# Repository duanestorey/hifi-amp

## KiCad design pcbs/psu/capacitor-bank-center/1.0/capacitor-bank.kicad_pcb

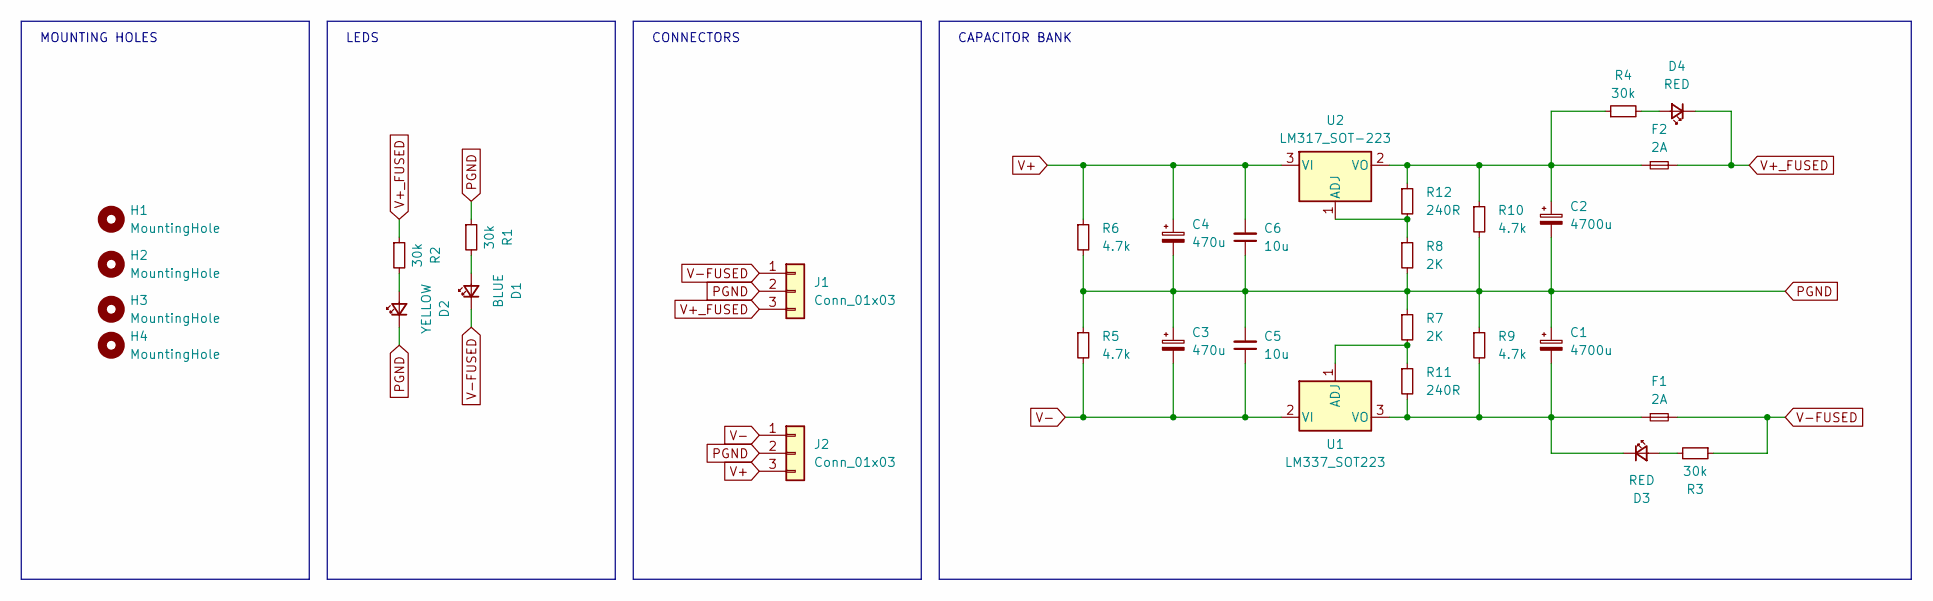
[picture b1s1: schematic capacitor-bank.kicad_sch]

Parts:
C1, C2: 4700u; CP_Radial_D16.0mm_P7.50mm
C3, C4: 470u; CP_Radial_D8.0mm_P5.00mm
C5, C6: 10u; C_1206_3216Metric_Pad1.33x1.80mm_HandSolder
D1: BLUE; LED_0805_2012Metric_Pad1.15x1.40mm_HandSolder
D2: YELLOW; LED_0805_2012Metric_Pad1.15x1.40mm_HandSolder
D3, D4: RED; LED_0805_2012Metric_Pad1.15x1.40mm_HandSolder
F1, F2: 2A; Aliexpress Fuse 5x20
H1, H2, H3, H4: MountingHole; MountingHole_3.2mm_M3_DIN965_Pad_TopBottom
J1, J2: Conn_01x03; JST_VH_B3P-VH-B_1x03_P3.96mm_Vertical
R1, R2, R3, R4: 30k; R_0805_2012Metric_Pad1.20x1.40mm_HandSolder
R5, R6, R9, R10: 4.7k; R_0805_2012Metric_Pad1.20x1.40mm_HandSolder
R7, R8: 2K; R_0805_2012Metric_Pad1.20x1.40mm_HandSolder
R11, R12: 240R; R_0805_2012Metric_Pad1.20x1.40mm_HandSolder
U1: LM337_SOT223; SOT-223-3_TabPin2
U2: LM317_SOT-223; SOT-223-3_TabPin2

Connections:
unnamed: D1.2 (A), R1.2
unnamed: D2.2 (A), R2.2
unnamed: D3.2 (A), R3.2
unnamed: C1.2, D3.1 (K), F1.1, R9.2, R11.2, U1.3 (VO)
unnamed: D4.2 (A), R4.2
unnamed: R7.2, R11.1, U1.1 (ADJ)
unnamed: R8.1, R12.2, U2.1 (ADJ)
unnamed: C2.1, F2.1, R4.1, R10.1, R12.1, U2.2 (VO)
PGND: C1.1, C2.2, C3.1, C4.2, C5.2, C6.1, D2.1 (K), J1.2, J2.2, R1.1, R5.1, R6.2, R7.1, R8.2, R9.1, R10.2
V+: C4.1, C6.2, J2.3, R6.1, U2.3 (VI)
V+_FUSED: D4.1 (K), F2.2, J1.3, R2.1
V-: C3.2, C5.1, J2.1, R5.2, U1.2 (VI)
V-FUSED: D1.1 (K), F1.2, J1.1, R3.1

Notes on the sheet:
CAPACITOR BANK
MOUNTING HOLES
LEDS
CONNECTORS

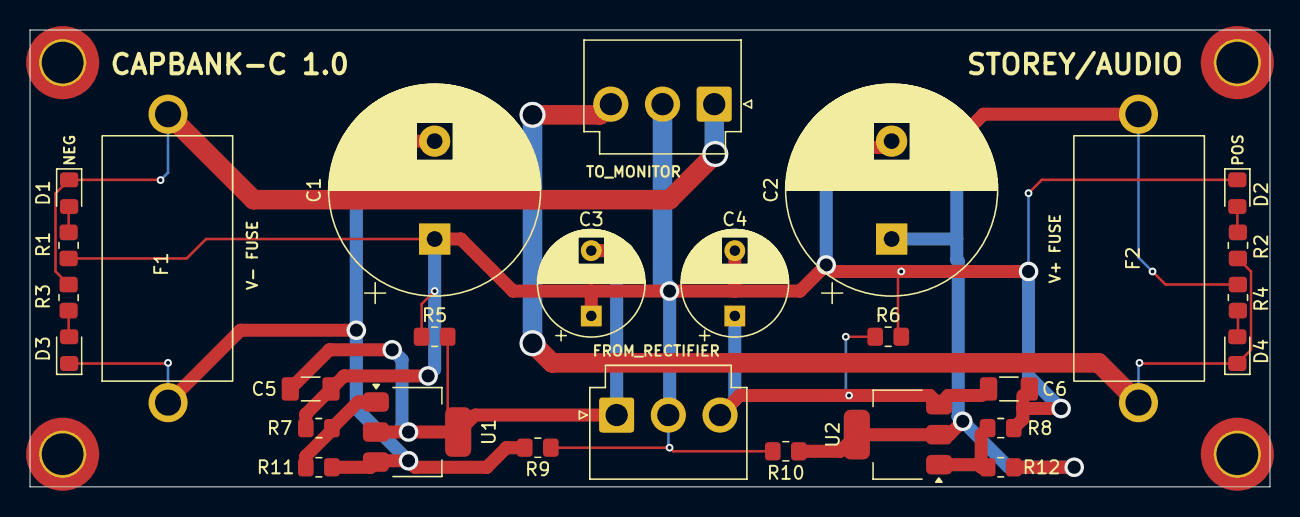
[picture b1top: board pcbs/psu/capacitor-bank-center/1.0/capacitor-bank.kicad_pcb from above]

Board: 2 copper layers, 95.0 x 35.0 mm, 32 parts (0 on the bottom side), 13 nets.

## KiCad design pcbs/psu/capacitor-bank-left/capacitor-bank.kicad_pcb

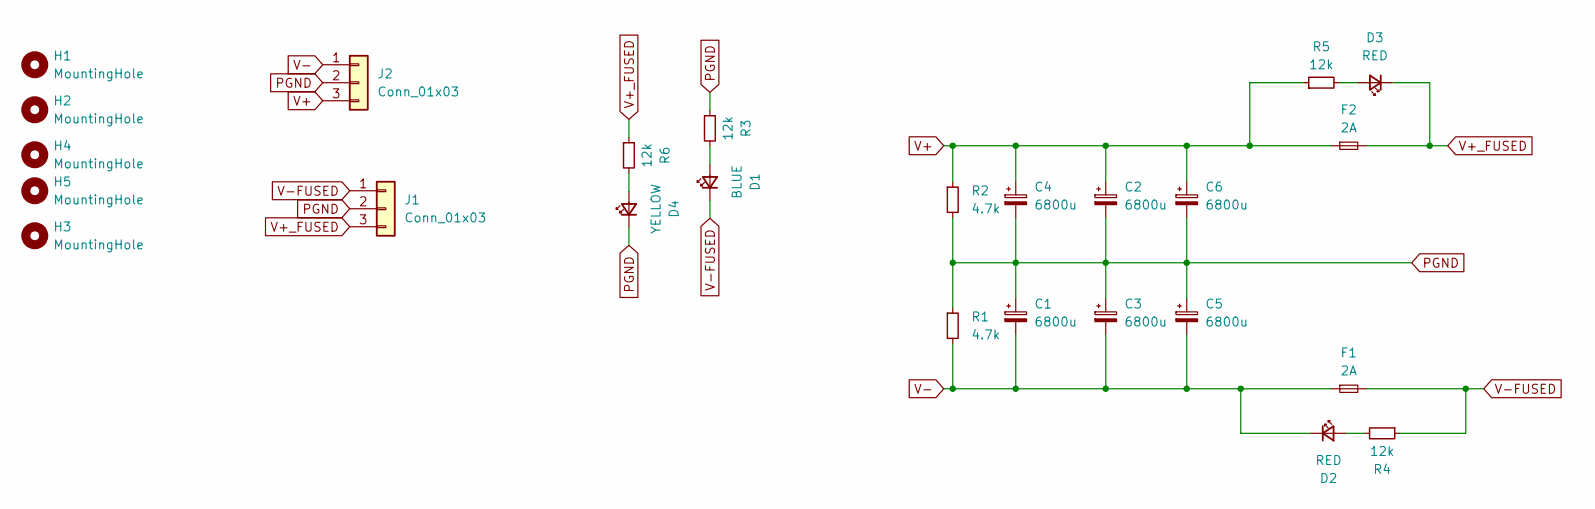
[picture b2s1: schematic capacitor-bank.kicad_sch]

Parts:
C1, C2, C3, C4, C5, C6: 6800u; CP_Radial_D25.0mm_P10.00mm_SnapIn
D1: BLUE; LED_0805_2012Metric_Pad1.15x1.40mm_HandSolder
D2, D3: RED; LED_0805_2012Metric_Pad1.15x1.40mm_HandSolder
D4: YELLOW; LED_0805_2012Metric_Pad1.15x1.40mm_HandSolder
F1, F2: 2A; Aliexpress Fuse 5x20
H1, H2, H3, H4, H5: MountingHole; MountingHole_3.2mm_M3_DIN965_Pad_TopBottom
J1, J2: Conn_01x03; JST_VH_B3P-VH-B_1x03_P3.96mm_Vertical
R1, R2: 4.7k; R_0805_2012Metric_Pad1.20x1.40mm_HandSolder
R3, R4, R5, R6: 12k; R_0805_2012Metric_Pad1.20x1.40mm_HandSolder

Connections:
unnamed: D1.2 (A), R3.2
unnamed: D2.2 (A), R4.2
unnamed: D3.2 (A), R5.2
unnamed: D4.2 (A), R6.2
PGND: C1.1, C2.2, C3.1, C4.2, C5.1, C6.2, D4.1 (K), J1.2, J2.2, R1.1, R2.2, R3.1
V+: C2.1, C4.1, C6.1, F2.1, J2.3, R2.1, R5.1
V+_FUSED: D3.1 (K), F2.2, J1.3, R6.1
V-: C1.2, C3.2, C5.2, D2.1 (K), F1.1, J2.1, R1.2
V-FUSED: D1.1 (K), F1.2, J1.1, R4.1

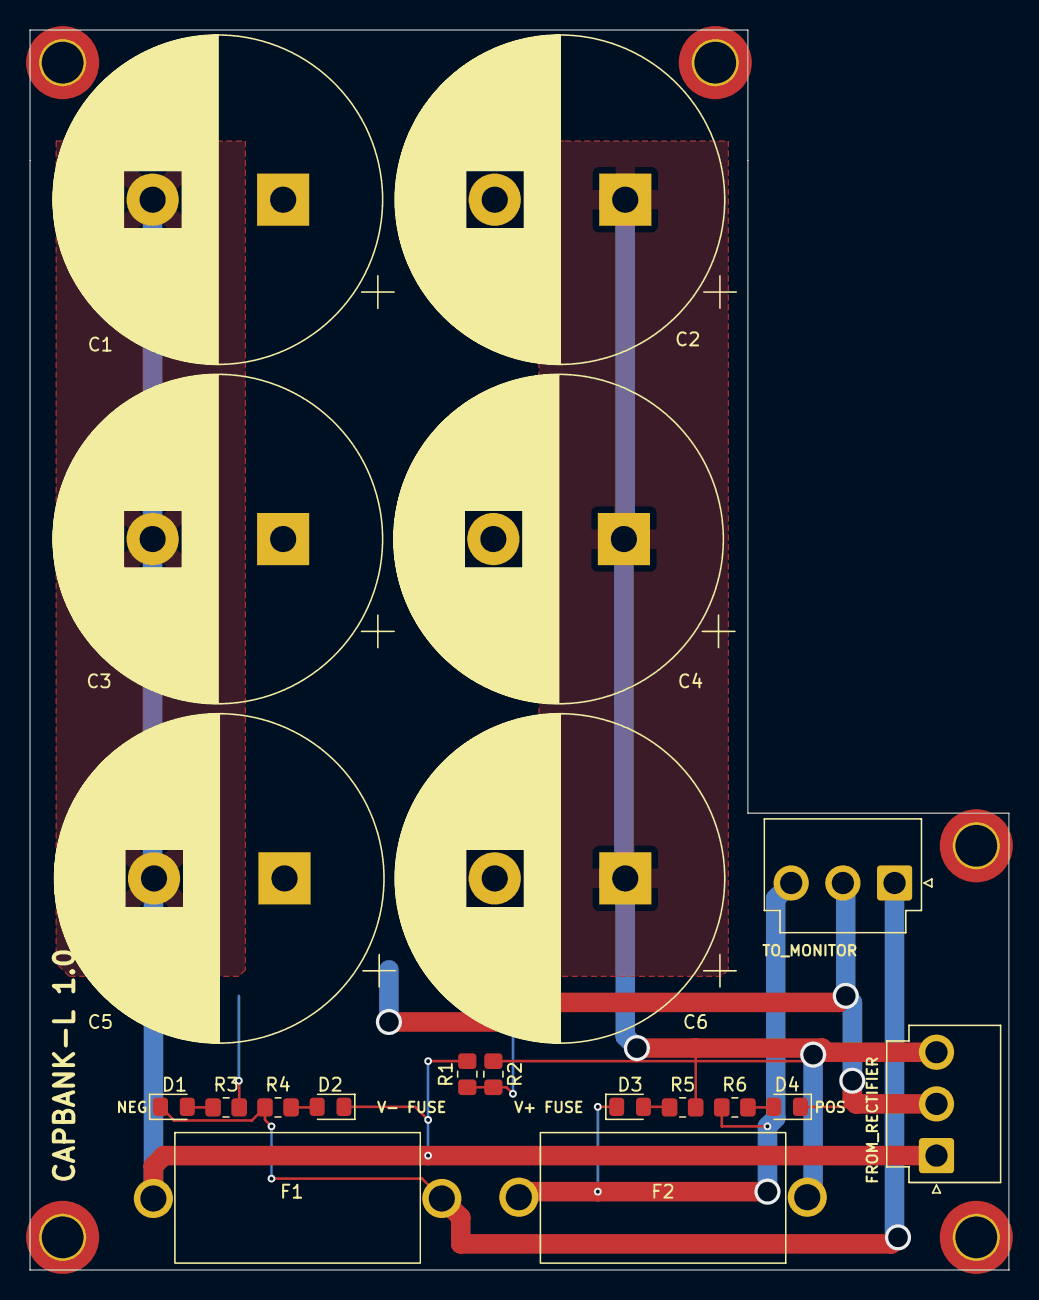
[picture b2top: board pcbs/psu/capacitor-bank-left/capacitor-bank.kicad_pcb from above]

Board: 2 copper layers, 75.0 x 95.0 mm, 25 parts (0 on the bottom side), 9 nets.

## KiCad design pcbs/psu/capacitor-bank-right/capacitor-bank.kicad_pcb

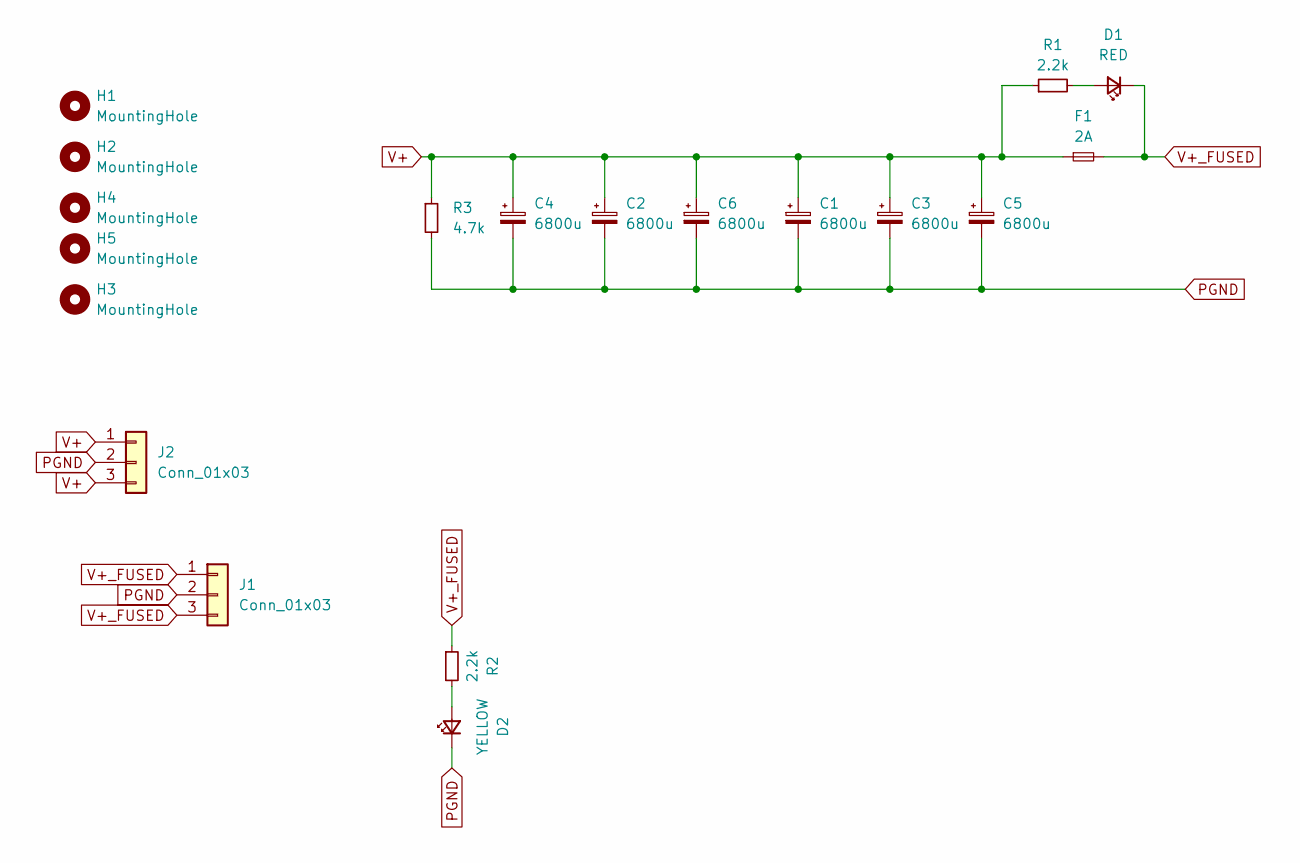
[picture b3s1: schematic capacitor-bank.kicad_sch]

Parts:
C1, C2, C3, C4, C5, C6: 6800u; CP_Radial_D25.0mm_P10.00mm_SnapIn
D1: RED; LED_0805_2012Metric_Pad1.15x1.40mm_HandSolder
D2: YELLOW; LED_0805_2012Metric_Pad1.15x1.40mm_HandSolder
F1: 2A; Aliexpress Fuse 5x20
H1, H2, H3, H4, H5: MountingHole; MountingHole_3.2mm_M3_DIN965_Pad_TopBottom
J1, J2: Conn_01x03; JST_VH_B3P-VH-B_1x03_P3.96mm_Vertical
R1, R2: 2.2k; R_0805_2012Metric_Pad1.20x1.40mm_HandSolder
R3: 4.7k; R_0805_2012Metric_Pad1.20x1.40mm_HandSolder

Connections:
unnamed: D1.2 (A), R1.2
unnamed: D2.2 (A), R2.2
PGND: C1.2, C2.2, C3.2, C4.2, C5.2, C6.2, D2.1 (K), J1.2, J2.2, R3.2
V+: C1.1, C2.1, C3.1, C4.1, C5.1, C6.1, F1.1, J2.1, J2.3, R1.1, R3.1
V+_FUSED: D1.1 (K), F1.2, J1.1, J1.3, R2.1

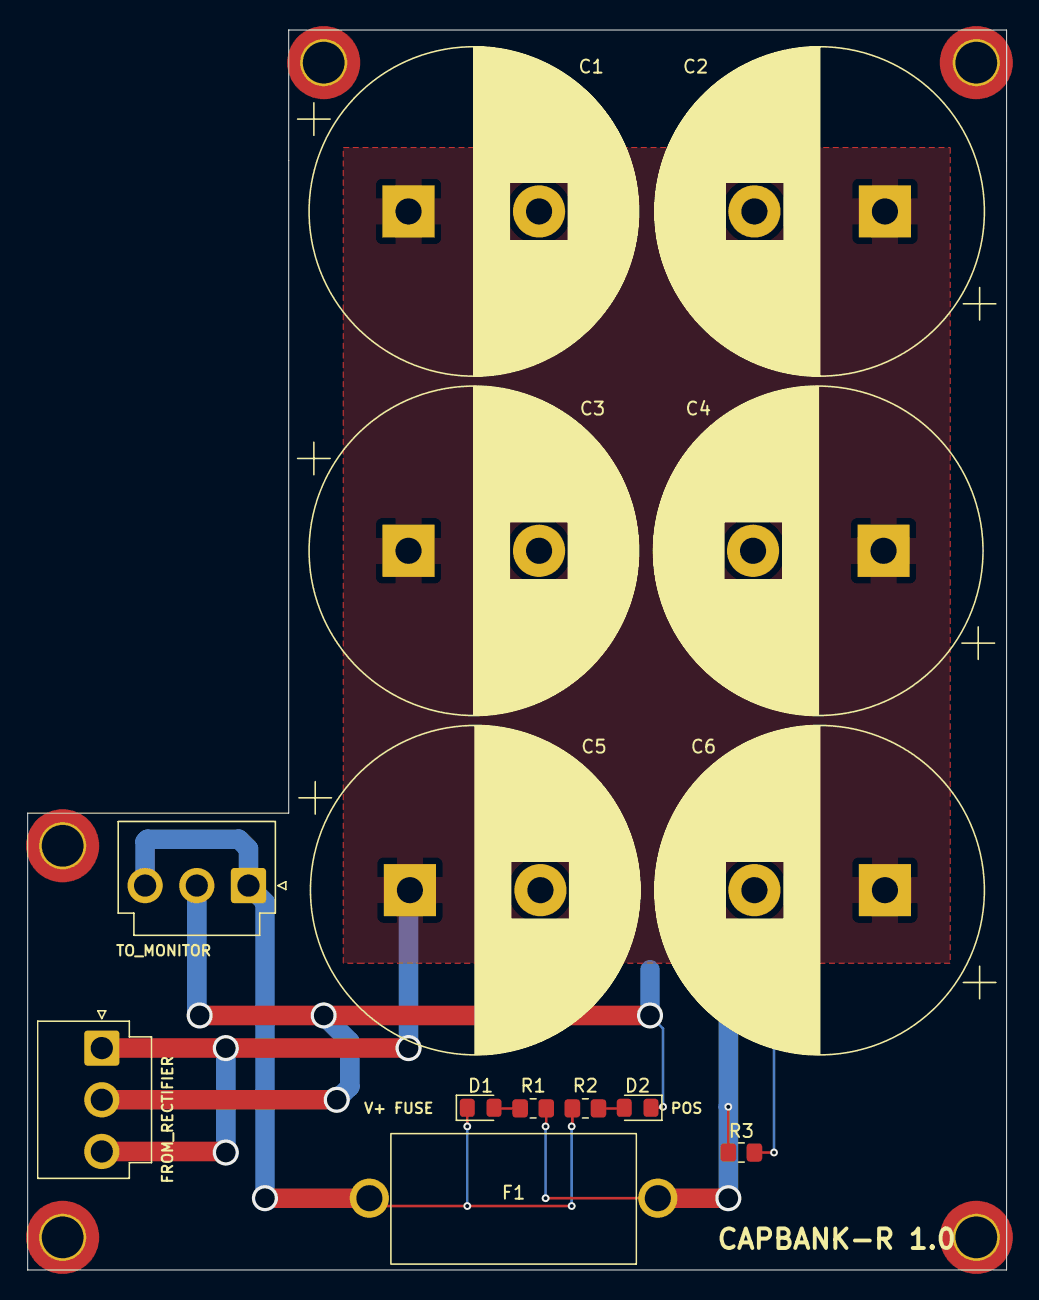
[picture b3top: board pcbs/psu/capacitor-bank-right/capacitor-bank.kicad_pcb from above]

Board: 2 copper layers, 75.0 x 95.0 mm, 19 parts (0 on the bottom side), 5 nets.

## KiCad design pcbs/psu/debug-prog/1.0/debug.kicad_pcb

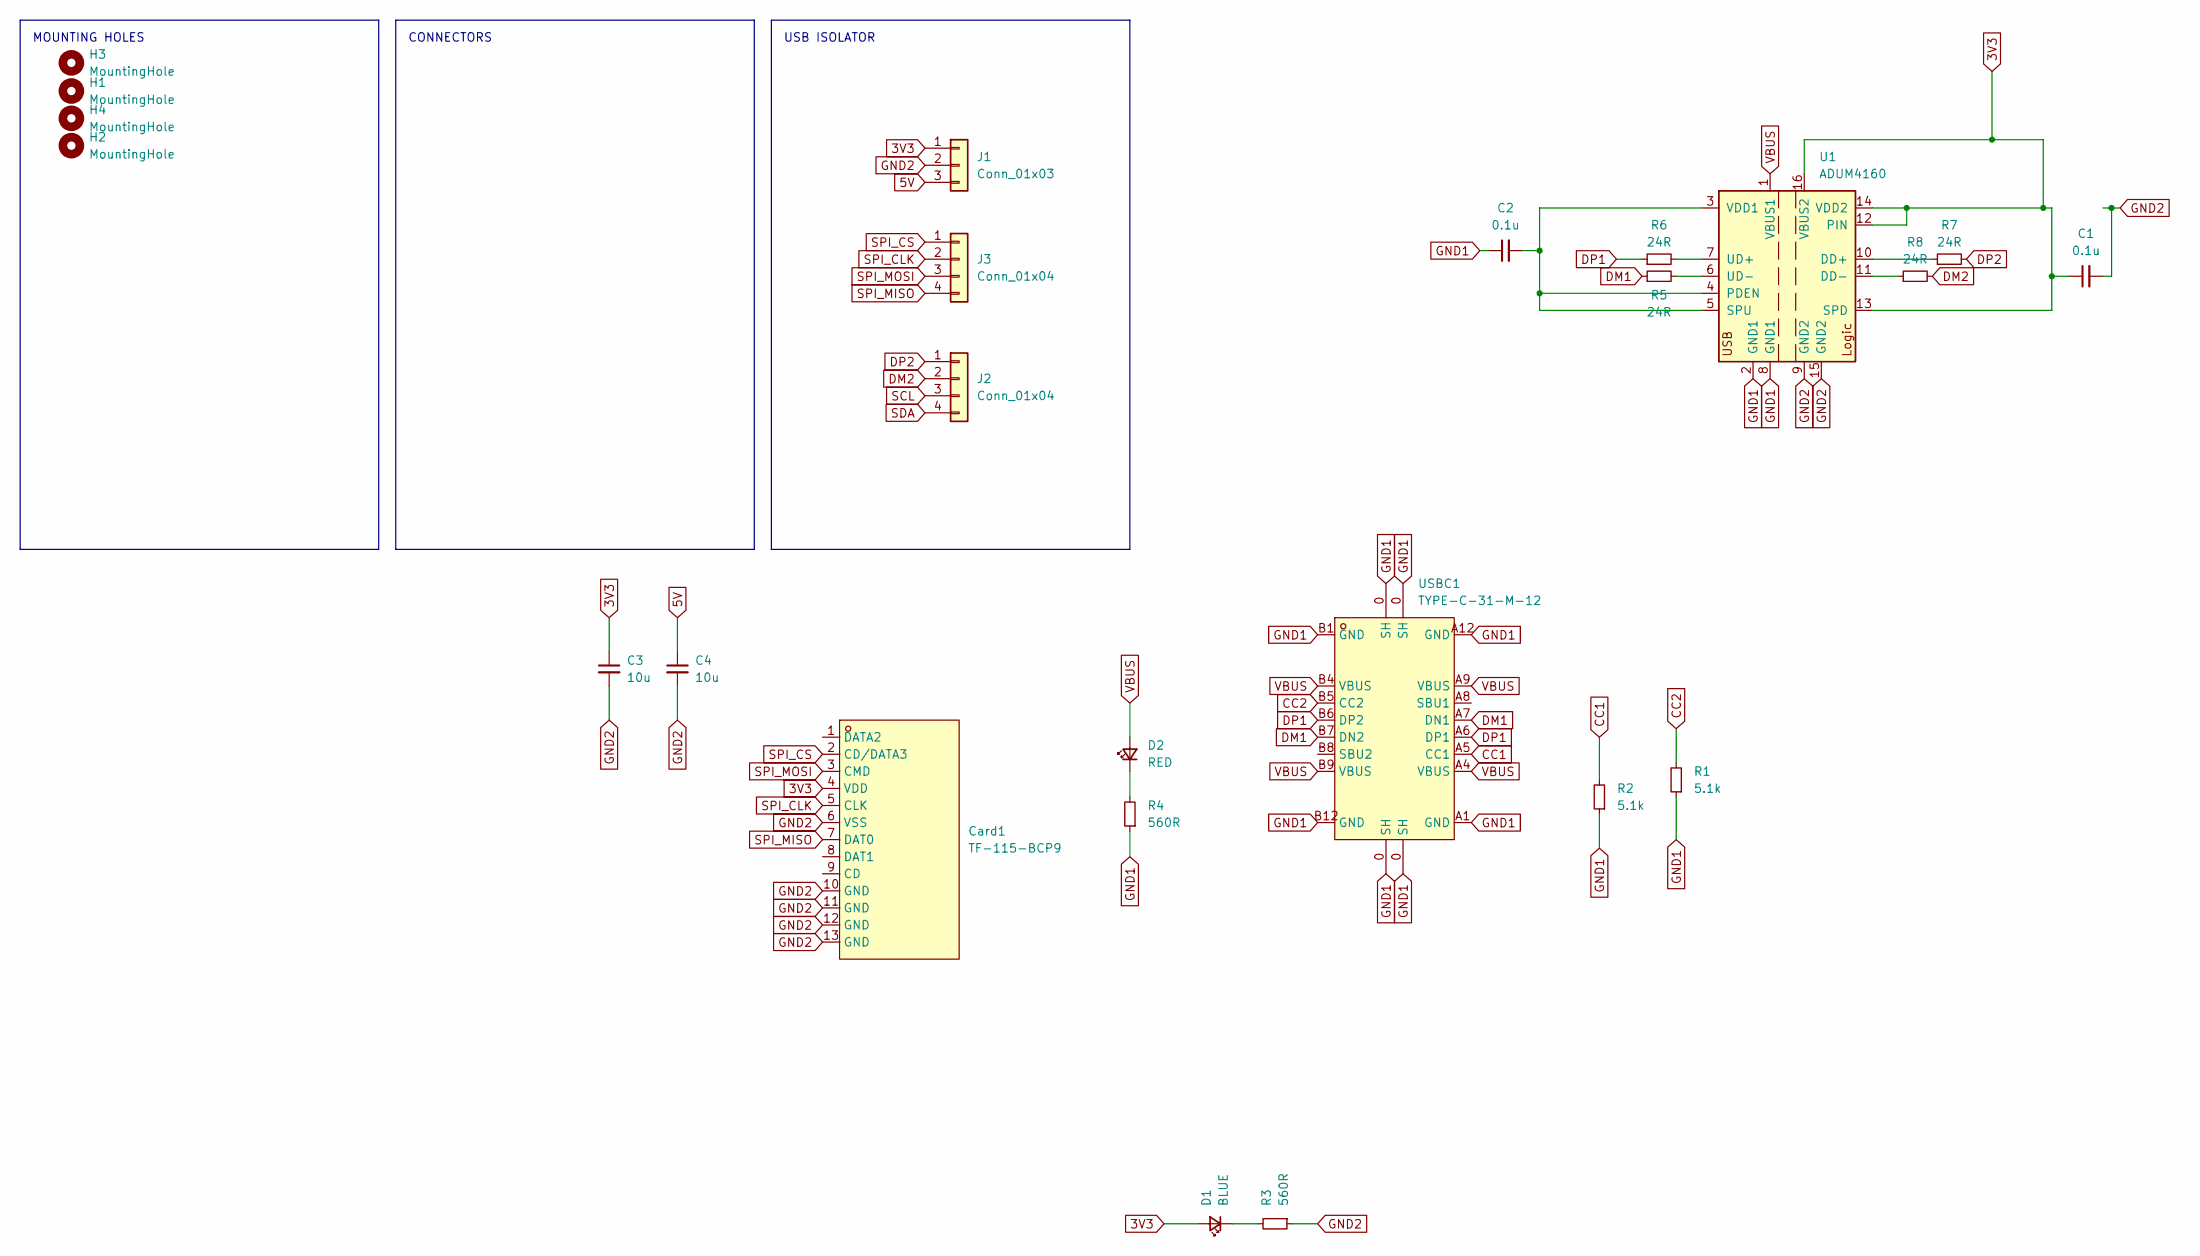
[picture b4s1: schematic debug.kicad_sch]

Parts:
C1, C2: 0.1u; C_0805_2012Metric_Pad1.18x1.45mm_HandSolder
C3, C4: 10u; C_1206_3216Metric_Pad1.33x1.80mm_HandSolder
Card1: TF-115-BCP9; TF-SMD_TF-115-BCP9; LCSC Part C720505
D1: BLUE; LED_0805_2012Metric_Pad1.15x1.40mm_HandSolder
D2: RED; LED_0805_2012Metric_Pad1.15x1.40mm_HandSolder
H1, H2, H3, H4: MountingHole; MountingHole_3.2mm_M3_DIN965_Pad_TopOnly
J1: Conn_01x03; JST_PH_B3B-PH-K_1x03_P2.00mm_Vertical
J2, J3: Conn_01x04; JST_PH_B4B-PH-K_1x04_P2.00mm_Vertical
R1, R2: 5.1k; R_0805_2012Metric_Pad1.20x1.40mm_HandSolder
R3, R4: 560R; R_0805_2012Metric_Pad1.20x1.40mm_HandSolder
R5, R6, R7, R8: 24R; R_0603_1608Metric_Pad0.98x0.95mm_HandSolder
U1: ADUM4160; SOIC-16W_7.5x10.3mm_P1.27mm
USBC1: TYPE-C-31-M-12; USB-C_SMD-TYPE-C-31-M-12; LCSC Part C165948

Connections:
3V3: C1.1, C3.1, Card1.4 (VDD), D1.2 (A), J1.1, U1.12 (PIN), U1.13 (SPD), U1.14 (VDD2), U1.16 (VBUS2)
5V: C4.1, J1.3
CC1: R2.2, USBC1.A5 (CC1)
CC2: R1.2, USBC1.B5 (CC2)
DM1: R5.1, USBC1.A7 (DN1), USBC1.B7 (DN2)
DM2: J2.2, R8.2
DP1: R6.1, USBC1.A6 (DP1), USBC1.B6 (DP2)
DP2: J2.1, R7.2
GND1: C2.1, R1.1, R2.1, R4.1, U1.2 (GND1), U1.8 (GND1), USBC1.0 (SH), USBC1.A1 (GND), USBC1.A12 (GND), USBC1.B1 (GND), USBC1.B12 (GND)
GND2: C1.2, C3.2, C4.2, Card1.6 (VSS), Card1.10 (GND), Card1.11 (GND), Card1.12 (GND), Card1.13 (GND), J1.2, R3.1, U1.9 (GND2), U1.15 (GND2)
unnamed: D1.1 (K), R3.2
unnamed: D2.1 (K), R4.2
unnamed: R7.1, U1.10 (DD+)
unnamed: R8.1, U1.11 (DD-)
unnamed: C2.2, U1.3 (VDD1), U1.4 (PDEN), U1.5 (SPU)
unnamed: R6.2, U1.7 (UD+)
unnamed: R5.2, U1.6 (UD-)
SCL: J2.3
SDA: J2.4
SPI_CLK: Card1.5 (CLK), J3.2
SPI_CS: Card1.2 (CD/DATA3), J3.1
SPI_MISO: Card1.7 (DAT0), J3.4
SPI_MOSI: Card1.3 (CMD), J3.3
VBUS: D2.2 (A), U1.1 (VBUS1), USBC1.A4 (VBUS), USBC1.A9 (VBUS), USBC1.B4 (VBUS), USBC1.B9 (VBUS)

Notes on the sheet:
CONNECTORS
USB ISOLATOR
MOUNTING HOLES

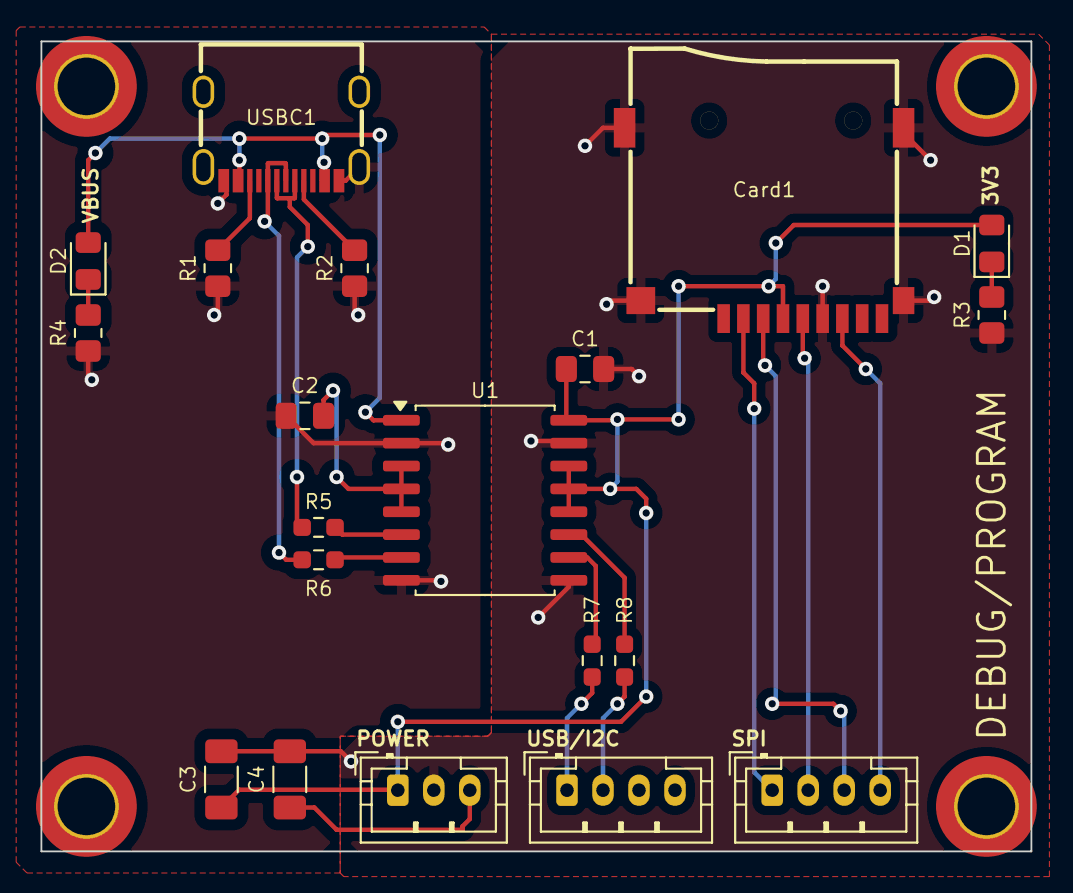
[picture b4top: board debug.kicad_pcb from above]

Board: 2 copper layers, 55.0 x 45.0 mm, 24 parts (0 on the bottom side), 22 nets.

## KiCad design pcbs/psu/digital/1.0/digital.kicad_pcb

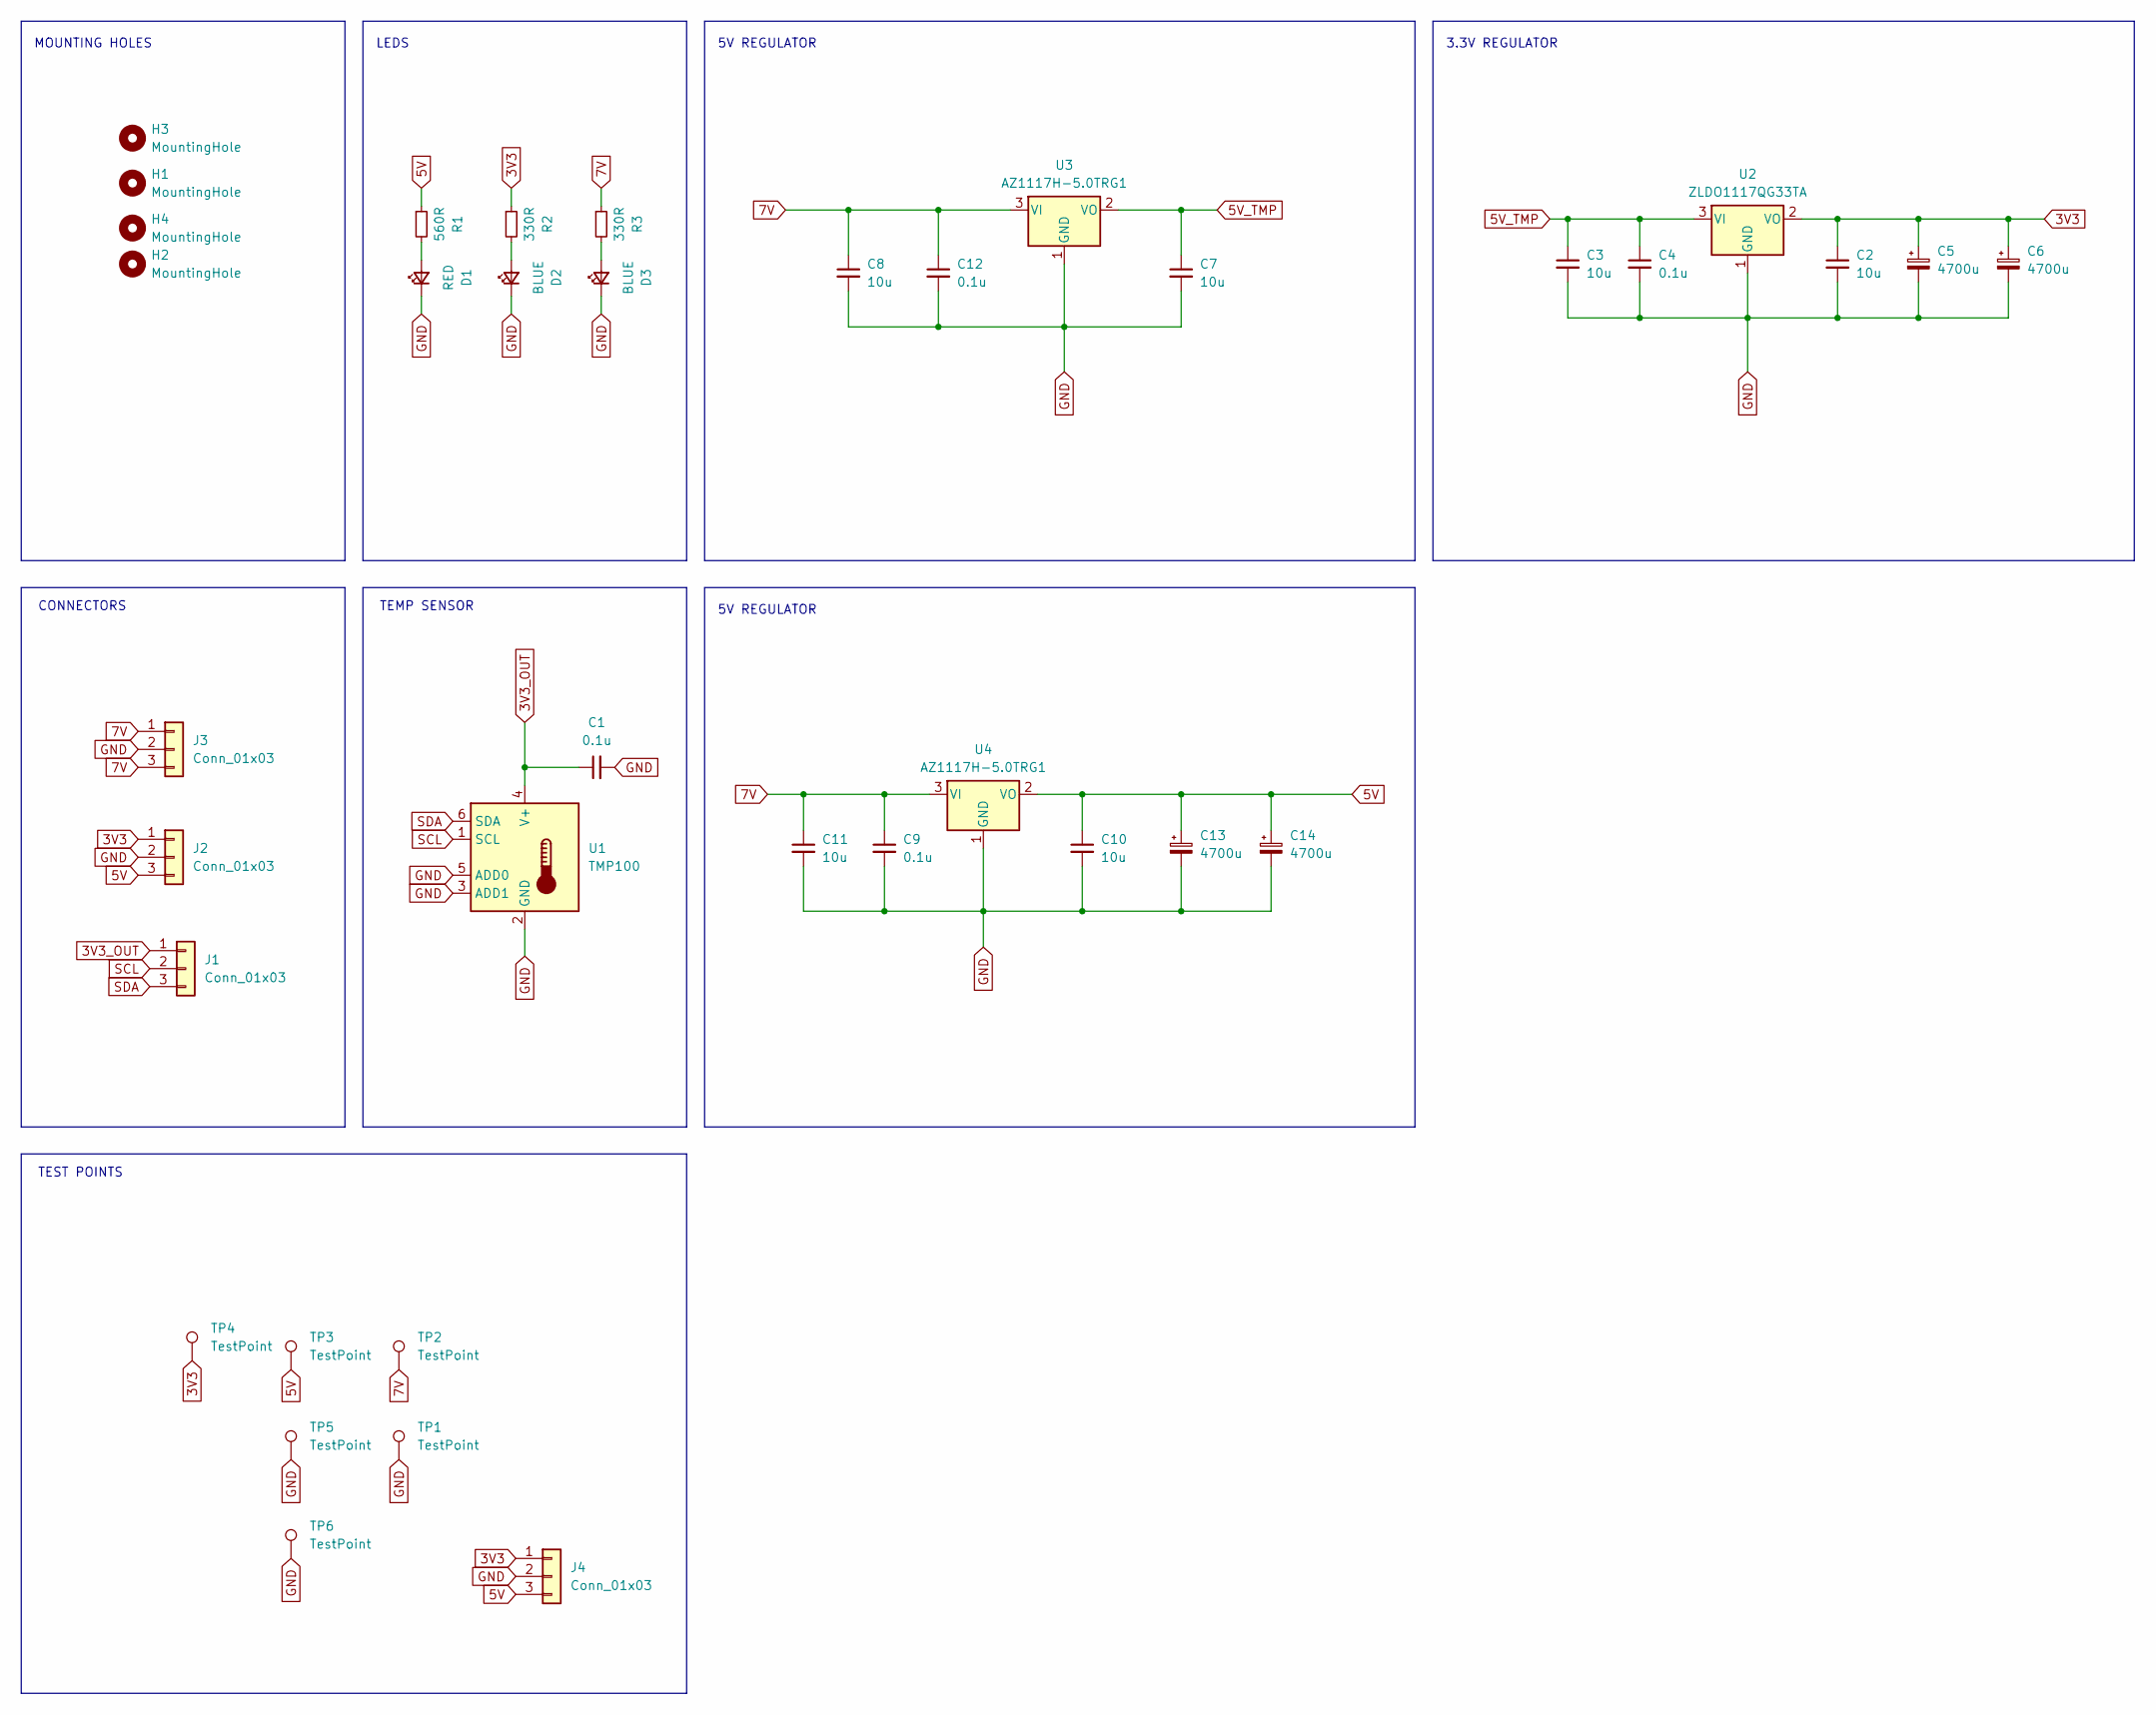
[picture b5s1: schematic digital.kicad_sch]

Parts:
C1, C4, C9, C12: 0.1u; C_0805_2012Metric_Pad1.18x1.45mm_HandSolder
C2, C3, C7, C8, C10, C11: 10u; C_1206_3216Metric_Pad1.33x1.80mm_HandSolder
C5, C6, C13, C14: 4700u; CP_Radial_D16.0mm_P7.50mm
D1: RED; LED_0805_2012Metric_Pad1.15x1.40mm_HandSolder
D2, D3: BLUE; LED_0805_2012Metric_Pad1.15x1.40mm_HandSolder
H1, H2, H3, H4: MountingHole; MountingHole_3.2mm_M3_DIN965_Pad_TopBottom
J1, J4: Conn_01x03; JST_PH_B3B-PH-K_1x03_P2.00mm_Vertical
J2, J3: Conn_01x03; JST_VH_B3P-VH-B_1x03_P3.96mm_Vertical
R1: 560R; R_0805_2012Metric_Pad1.20x1.40mm_HandSolder
R2, R3: 330R; R_0805_2012Metric_Pad1.20x1.40mm_HandSolder
TP1, TP2, TP3, TP4, TP5, TP6: TestPoint; TestPoint_THTPad_2.5x2.5mm_Drill1.2mm
U1: TMP100; SOT-23-6
U2: ZLDO1117QG33TA; SOT-223; Mouser ZLDO1117QG33TA
U3, U4: AZ1117H-5.0TRG1; SOT-223

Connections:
3V3: C2.1, C5.1, C6.1, J2.1, J4.1, R2.1, TP4.1, U2.2 (VO)
3V3_OUT: C1.1, J1.1, U1.4 (V+)
5V: C10.1, C13.1, C14.1, J2.3, J4.3, R1.1, TP3.1, U4.2 (VO)
5V_TMP: C3.1, C4.1, C7.1, U2.3 (VI), U3.2 (VO)
7V: C8.1, C9.1, C11.1, C12.1, J3.1, J3.3, R3.1, TP2.1, U3.3 (VI), U4.3 (VI)
GND: C1.2, C2.2, C3.2, C4.2, C5.2, C6.2, C7.2, C8.2, C9.2, C10.2, C11.2, C12.2, C13.2, C14.2, D1.1 (K), D2.1 (K), D3.1 (K), J2.2, J3.2, J4.2, TP1.1, TP5.1, TP6.1, U1.2 (GND), U1.3 (ADD1), U1.5 (ADD0), U2.1 (GND), U3.1 (GND), U4.1 (GND)
unnamed: D1.2 (A), R1.2
unnamed: D2.2 (A), R2.2
unnamed: D3.2 (A), R3.2
SCL: J1.2, U1.1 (SCL)
SDA: J1.3, U1.6 (SDA)

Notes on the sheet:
TEST POINTS
3.3V REGULATOR
5V REGULATOR
LEDS
TEMP SENSOR
MOUNTING HOLES
CONNECTORS

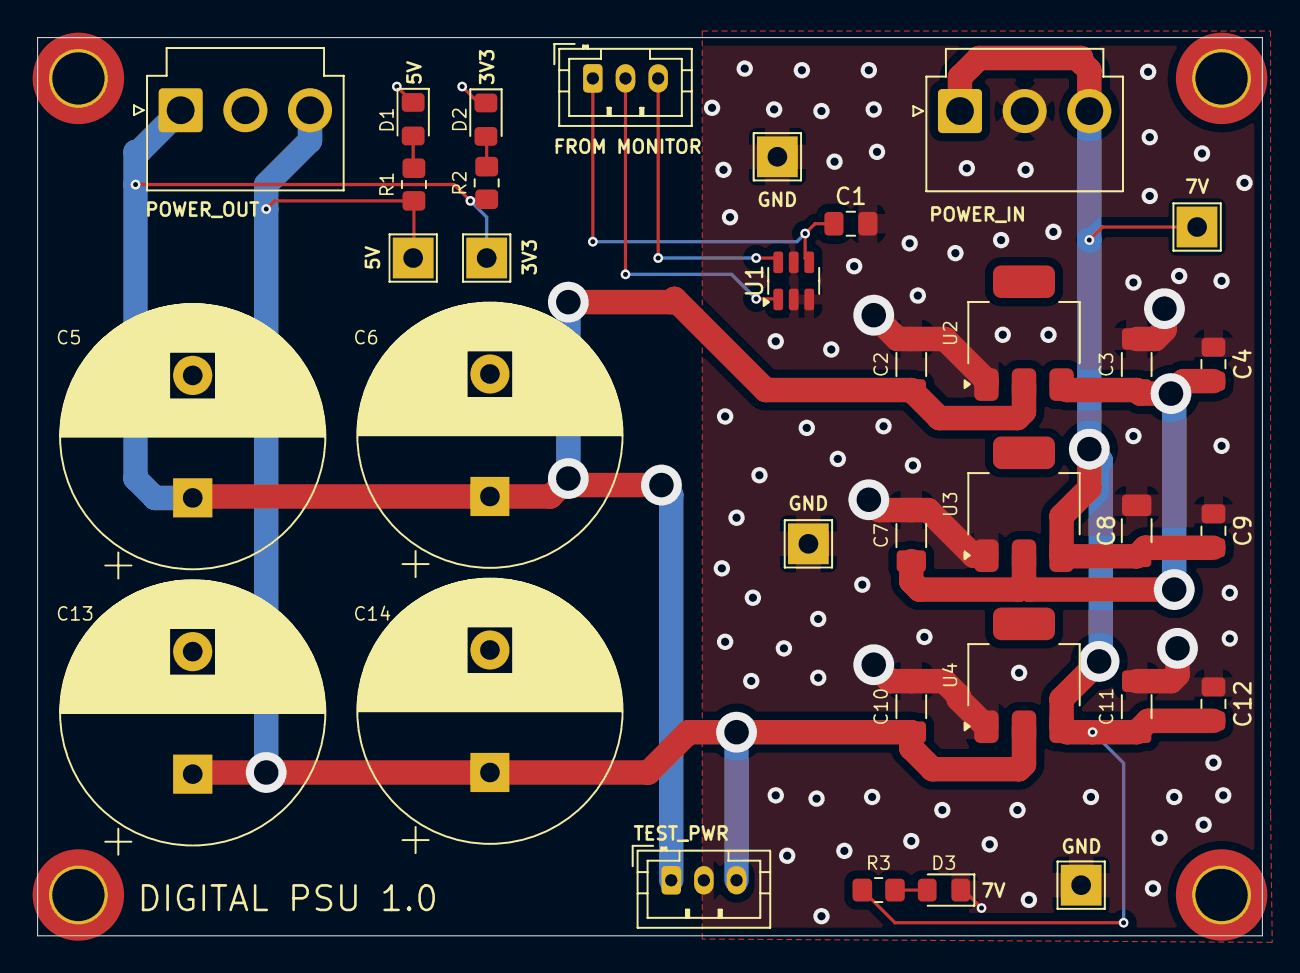
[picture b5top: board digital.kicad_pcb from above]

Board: 2 copper layers, 75.0 x 55.0 mm, 38 parts (0 on the bottom side), 11 nets.
